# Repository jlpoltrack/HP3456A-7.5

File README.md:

# HP 3456A 7.5-Digit Firmware, Fixed

A corrected build of the community 7.5-digit firmware for the HP 3456A digital voltmeter.

The 7.5-digit mod, shared in the EEVblog thread "Adventures in retrocomputing"
(`3456AFirmware.zip`), shows a 7th digit at 10 and 100 PLC. Its published ROM also has seven
bugs. They crept in when the disassembly was restructured, and the best known is an **autorange
freeze**. This build fixes all seven, keeps the 7.5-digit feature, and tightens when the 7th
digit appears.

**Status:** tested on a real meter on 2026-10-19. All front-panel tests pass; see
[`docs/HARDWARE_VALIDATION.md`](docs/HARDWARE_VALIDATION.md). HPIB output of the 7th digit
has not been tested on hardware yet.

## What you get

- **7th digit** at 10 and 100 PLC, in the display's exponent position.
- **Autorange that works:** the meter ranges up and down without freezing.
- **Factory behaviour restored** for error 4 on bad digit counts, the dBm reference, NULL, the
  R and U presets, and storing the delay register D.

## Using 7-digit mode

Set 10 or 100 PLC, then enter `7` for digits displayed. The 7th digit is hidden, and the meter
behaves as a stock 6.5-digit unit, when:

- PLC is 1 or lower (the extra digit would only be noise);
- a number is being entered on the keypad or over HPIB.

### Reading the display

The 7th digit replaces the exponent, and the exponent sign is blank. Read the six mantissa digits
and append the 7th.

- **One decimal point lit:** no exponent is hidden, so read the value as shown.
- **Every decimal point lit except one:** the 7th digit is hiding an exponent. The digit with
  the **dark** decimal point is the true decimal position. The exponent is whatever the same
  range shows at 1 PLC, so check it once for each range you use.

Example: DCV, 100 mV range, shorted input, 10 PLC, 7 digits:

```
display   - 0. 0  0. 0. 0. 4.   7      dark DP after digit 2; at 1 PLC the range shows E-3
reads     -00.00047 E-3 V  = -0.47 µV  (10 nV resolution)
```

## Bugs fixed

None of these are in the factory ROM. Each was found by comparing against the factory `u7.bin`
and is tagged `FIX:` in [`src/u7fixed.asm`](src/u7fixed.asm).

| Where | Bug | Effect in the published ROM |
| --- | --- | --- |
| `sub012` (LA70F, LA724) | `jmp LC9D2` (main-loop restart) instead of `rts` | **Autorange freeze:** the new range never reaches the inguard |
| Power-on init (LD9A1) | 600 Ω preset written to the null register Z instead of R | Z = 600 and R = 0 after power-on |
| `subMathFcnDBM` | Tests Z instead of R for zero | The dBm guard checks the wrong register |
| `subPresetLnUregs` | U exponent written to U5 instead of U6 | Upper limit U is wrong (should be +1.999999E9) |
| RECALL key (LF4B8) | Clears Z0 instead of R0 | Wrong register cleared |
| Register D entry (LE0BC) | `bcc LE191` became an unconditional `jmp LE191` | Valid delay values are never stored |
| Digits-displayed entry (LE1DE) | `jsr subDisplayError4` dropped | Entering 2 or 8 is silently ignored instead of showing E4 |

The 7th-digit display and HPIB output now go through one routine, `sub7thDigitShown`, which
applies the PLC and number-entry rules above.

## Build

Requires Python 3.

```
python3 tools/as02.py src/u7fixed.asm build/u7fixed.bin build/u7fixed.lst
```

`build/u7fixed.bin` is a 32 KB image for U7, with the same layout as the original. For a larger
chip, tile it so the image works whatever the unused upper address lines are tied to:

```
python3 tools/replicate.py build/u7fixed.bin build/u7fixed_512K.bin 512K
```

Expected hashes for the tested build are listed in `docs/HARDWARE_VALIDATION.md`.

## Install

The validated meter uses an SST39SF040 flash chip, wired as a 27256-style ROM in the 28-pin U7
socket on the A4 controller board, and programmed with a TL866 (`minipro`). Wiring, continuity
checks and programming commands are in
[`docs/U7_FLASH_ADAPTER.md`](docs/U7_FLASH_ADAPTER.md). A PCB adapter that keeps the chip stock is in
[`hardware/u7-adapter/`](hardware/u7-adapter/) (designed, not yet built).

Before you install:

- **Back up the current chip** first (`minipro -p SST39SF040 -r backup.bin`).
- **Run the self-test** after installing. TEST cycles all segments on and off continuously
  until you press another key; a failure breaks the cycle and shows an error.

## ROM space

About 950 bytes are free for future changes:

| Range | Bytes | Notes |
| --- | --- | --- |
| $F33E–$F65A | 797 | Directly after the code |
| $FF56–$FFEF | 154 | Below the interrupt vectors |
| $8000–$9FFF | 8192 | Never used by the factory ROM; whether the board maps it to U7 is unverified |

### Ideas for the free space

Contributions welcome. Sizes are rough estimates.

| Idea | Size | Why |
| --- | --- | --- |
| Firmware version at power-on (e.g. `FIX 1` after `+HP3456+`) | ~30 B | Tells you which ROM a meter is running |
| ROM checksum in self-test | ~60 B | Catches a bad flash or failing chip, which the current self-test can't |
| Power-on defaults (e.g. 10 PLC, 7 digits) | ~20 B | The meter has no settings memory |
| ppm deviation math mode | ~150–250 B | % error has too few digits for 7.5-digit drift and calibration work |
| Stability indicator | ~100–150 B | Annunciator lights once the last N readings agree within X counts |
| Min/max hold | ~100 B | Track the extremes, viewable with RECALL L / U |
| Pt100 RTD temperature | ~300–400 B | 4-wire ohms to °C (Callendar–Van Dusen), using the ROM's BCD maths |

The first three fit together in the 154-byte block below the vectors, leaving the 797-byte
block for one larger feature.

To try out code in $8000–$9FFF, a [One ROM](https://onerom.org/) Fire 28 in place of the flash
chip makes testing and rollback fast. See the end of `docs/HARDWARE_VALIDATION.md`.

## Repository layout

| Path | Contents |
| --- | --- |
| `src/u7fixed.asm` | Fixed source; changes tagged `FIX:` (this build) and `MODDED` (the original 7.5-digit mod) |
| `src/u7modded.asm` | The published mod's source, recovered from its listing (the zip has no `.asm`); reassembles byte-identical to `u7modded.bin` |
| `tools/as02.py` | 6800 assembler for the AS02 subset used here, with branch relaxation |
| `tools/compare.py` | Lockstep semantic diff of two ROMs: `compare.py orig.bin new.bin new.lst`. Run it against the factory `u7.bin` |
| `tools/dis.py` | Linear 6800 disassembler: `dis.py rom.bin start end` |
| `tools/replicate.py` | Tiles an image to fill a larger chip |
| `tools/lst2asm.py` | Recovers source from an AS02 listing |
| `tools/patch.py` | Earlier in-place binary patcher, superseded by the source build |
| `hardware/u7-adapter/` | KiCad project for the U7 flash adapter PCB: SST39SF040 socket on a DIP-28 plug, bank jumpers |
| `docs/` | Flash adapter wiring, the hardware test plan with results, and the [HP-IB command reference](docs/GPIB_COMMANDS.md) |

## Credits, license and disclaimer

The disassembly, commentary and 7.5-digit mod come from the work shared in the EEVblog
"Adventures in retrocomputing" thread. This project only fixes and extends it. The original
firmware is HP's.

This project's own work (the tools, the docs and the `FIX:` changes) is MIT-licensed; see
[`LICENSE`](LICENSE). The licence doesn't cover HP's firmware or the upstream mod. No ROM
images are included: get `3456AFirmware.zip` from the thread, then build from source.

Use at your own risk. Back up your original ROM, and work only on the outguard controller
board with the meter unplugged.

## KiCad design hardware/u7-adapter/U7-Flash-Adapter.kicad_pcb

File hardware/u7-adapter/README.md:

# U7 Flash Adapter

A small PCB that runs an SST39SF040 flash chip in the 28-pin U7 socket of the HP 3456A A4 controller
board. It replaces the hand-wired chip in [`docs/U7_FLASH_ADAPTER.md`](../../docs/U7_FLASH_ADAPTER.md):
the flash chip stays stock, so it moves between the adapter and the TL866 without bending any legs.

**Status (2026-10-24):** V1.0, designed and checked (DRC, ERC and lint all clean). Not yet ordered
or tested in a meter. See [Open items](#open-items) before ordering.

| Front | Back |
| --- | --- |
|  |  |

## How it works

- **Plug (J2):** a DIP-28 pin pattern under the board plugs into U7. It uses the 27256 pinout,
  and pin 1 (VPP) is not connected.
- **Socket (U1):** the 32-pin socket sits 5.1 mm to the right of the plug and two rows higher, so
  plug pin *n* and flash pin *n*+2 share a row. All 26 signals and GND are one straight trace each.
- **Read-only:** WE# is tied to +5V, so the chip is never written in the meter.
- **Power:** there are two ways to feed +5V, and the board ships with neither connected.
  - **JP1** (silk `P28`) joins U7 pin 28 to +5V. It is open as built. Bridge it only after U7
    pin 28 measures +5 V with the meter on and the chip out. Nobody has checked yet what the A4
    board puts on that pin.
  - **TP1** (silk `C1+`) is a wire pad. Run a wire from it to the + end of the meter's C1, the
    same way the hand-wired chip is powered.

  C1 on the adapter (100 nF) decouples U1 pin 32.
- **Bank select (J1):** 10k resistors (R1–R4) pull A15–A18 low, so with no jumpers the chip reads
  bank 0 (the first 32K). A jumper from an A pin to the 5V pin above it sets that bit to 1.
  Bank *n* is the 32K block at offset *n* × $8000. The columns are labelled A18 A16 A15 A17, in
  routing order. `u7fixed_512K.bin` repeats the image in all 16 banks, so jumpers only matter if
  you store different images.

## Parts

| Ref | Part | Notes |
| --- | --- | --- |
| U1 | 32-pin 600 mil turned-pin DIP socket | holds the SST39SF040 |
| J2 | 28-pin 600 mil DIP plug: two 1x14 machined male pin strips, or a machined-pin DIP header | soldered from the bottom, long pins down into U7 |
| J1 | 2x4 pin header, 2.54 mm, plus jumpers | bank select |
| R1–R4 | 10k, 0805 | A15–A18 pull-downs |
| C1 | 100 nF, 0805, 25 V or more | decoupling |
| JP1 | solder jumper (on the PCB) | U7 pin 28 to +5V |
| TP1 | wire pad (on the PCB) | +5V from the meter's C1 |

A plain DIP socket can't be J2: its pins are too short to reach through the board into U7, and a
long-tail (wire-wrap) socket would need its body on top, where U1 sits.

## Assembly

1. Solder the 0805 parts (R1–R4, C1) first.
2. Fit J1.
3. Fit U1 on the top.
4. Fit J2 from the bottom, with the long pins pointing down. Solder J2 on the top, inside U1's
   open frame, before the chip goes in. The B silk shows J2's outline and pin-1 notch.
5. Power: either bridge JP1 (only once pin 28 is confirmed as +5 V), or wire TP1 to the meter's C1.
6. Before fitting it in the meter, with no chip in, check for no short from +5V to GND. Then check
   each J2 pin to its U1 pin, n to n+2.

U1's notch and J2's pin 1 both face the same end, toward the board edge as the chip sits now.

## Fabrication

2-layer, 1.6 mm, 29.4 x 54.2 mm, JLC default rules. Gerbers and drill files are in
`production/HP_3456A_U7_Flash_Adapter_1.0.zip`. It's a bare-PCB order: all parts are hand-soldered,
and the BOM and positions files are not needed. Five boards cost about $4 plus shipping.

## Files

| Path | Contents |
| --- | --- |
| `U7-Flash-Adapter.kicad_sch` / `.kicad_pcb` | KiCad 10 project |
| `U7-Flash-Adapter.pdf` | schematic |
| `production/` | gerbers and drill files (zip), BOM, positions |
| `renders/Routing-*.png`, `Render-Copper.png` | copper views |
| `style_lint.ignore` | accepted lint items (parts aligned to the 2.54 mm pin rows, off the 0.1 mm grid) |

The schematic and board were generated by scripts in the author's (private) kicad-tools repo
(`projects/u7-adapter/`). Edit the KiCad files directly; they are the source of truth here.
`pth_inside_courtyard` is set to ignore in the project, because the plug and the socket overlap by
design.

## Open items

- [ ] Measure U7 pin 28 against pin 14 with the chip out and the meter on, to decide JP1 or TP1.
- [ ] Measure the clearance around U7. The adapter overhangs U7: the board reaches about 5 mm past
      the plug on the right (the socket and C1 strip) and 18 mm past pin 1 (the bank header). It
      also sits about 12 mm higher than the bare chip.
- [ ] Order the PCB, build one, and run the checks in `docs/HARDWARE_VALIDATION.md`.

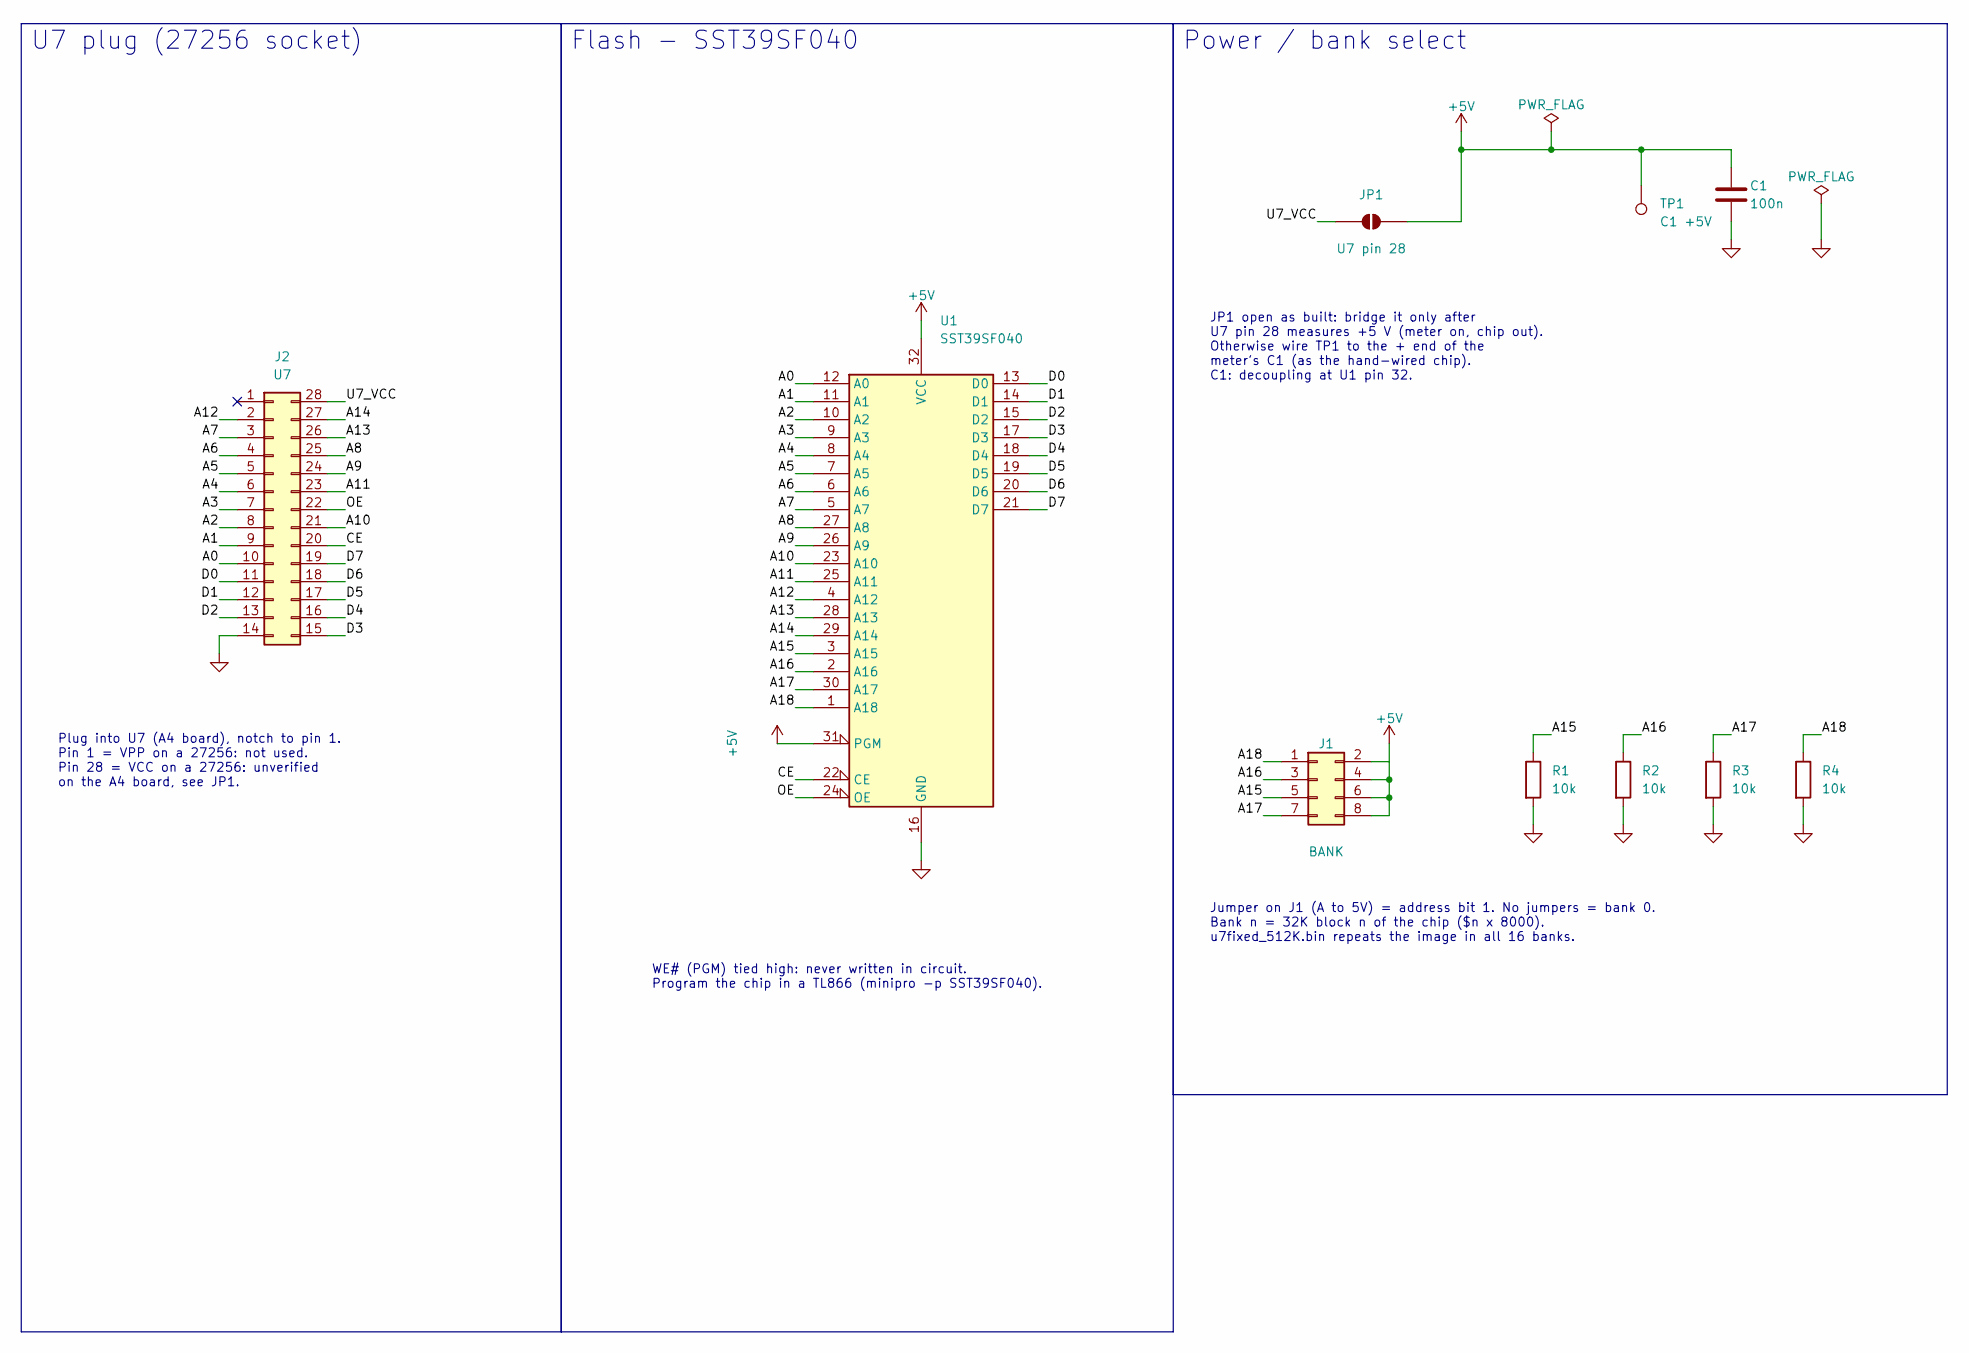
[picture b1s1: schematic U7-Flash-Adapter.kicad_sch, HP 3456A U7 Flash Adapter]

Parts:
C1: 100n; C_0805_2012Metric_Pad1.18x1.45mm_HandSolder
J1: BANK; PinHeader_2x04_P2.54mm_Vertical
J2: U7; DIP-28_W15.24mm_Plug
JP1: U7 pin 28; SolderJumper-2_P1.3mm_Open_TrianglePad1.0x1.5mm
R1, R2, R3, R4: 10k; R_0805_2012Metric_Pad1.20x1.40mm_HandSolder
TP1: C1 +5V; TestPoint_THTPad_D2.0mm_Drill1.0mm
U1: SST39SF040; DIP-32_W15.24mm_Socket

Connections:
+5V: C1.1, J1.2, J1.4, J1.6, J1.8, JP1.2 (B), TP1.1 (1_1), U1.31 (PGM), U1.32 (VCC)
/A0: J2.10, U1.12 (A0)
/A1: J2.9, U1.11 (A1)
/A2: J2.8, U1.10 (A2)
/A3: J2.7, U1.9 (A3)
/A4: J2.6, U1.8 (A4)
/A5: J2.5, U1.7 (A5)
/A6: J2.4, U1.6 (A6)
/A7: J2.3, U1.5 (A7)
/A8: J2.25, U1.27 (A8)
/A9: J2.24, U1.26 (A9)
/A10: J2.21, U1.23 (A10)
/A11: J2.23, U1.25 (A11)
/A12: J2.2, U1.4 (A12)
/A13: J2.26, U1.28 (A13)
/A14: J2.27, U1.29 (A14)
/A15: J1.5, R1.1, U1.3 (A15)
/A16: J1.3, R2.1, U1.2 (A16)
/A17: J1.7, R3.1, U1.30 (A17)
/A18: J1.1, R4.1, U1.1 (A18)
/CE: J2.20, U1.22 (CE)
/D0: J2.11, U1.13 (D0)
/D1: J2.12, U1.14 (D1)
/D2: J2.13, U1.15 (D2)
/D3: J2.15, U1.17 (D3)
/D4: J2.16, U1.18 (D4)
/D5: J2.17, U1.19 (D5)
/D6: J2.18, U1.20 (D6)
/D7: J2.19, U1.21 (D7)
/OE: J2.22, U1.24 (OE)
/U7_VCC: J2.28, JP1.1 (A)
GND: C1.2, J2.14, R1.2, R2.2, R3.2, R4.2, U1.16 (GND)

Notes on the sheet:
U7 plug (27256 socket)
Flash - SST39SF040
Power / bank select
Plug into U7 (A4 board), notch to pin 1. Pin 1 = VPP on a 27256: not used. Pin 28 = VCC on a 27256: unverified on the A4 board, see JP1.
WE# (PGM) tied high: never written in circuit. Program the chip in a TL866 (minipro -p SST39SF040).
JP1 open as built: bridge it only after U7 pin 28 measures +5 V (meter on, chip out). Otherwise wire TP1 to the + end of the meter's C1 (as the hand-wired chip). C1: decoupling at U1 pin 32.
Jumper on J1 (A to 5V) = address bit 1. No jumpers = bank 0. Bank n = 32K block n of the chip ($n x 8000). u7fixed_512K.bin repeats the image in all 16 banks.

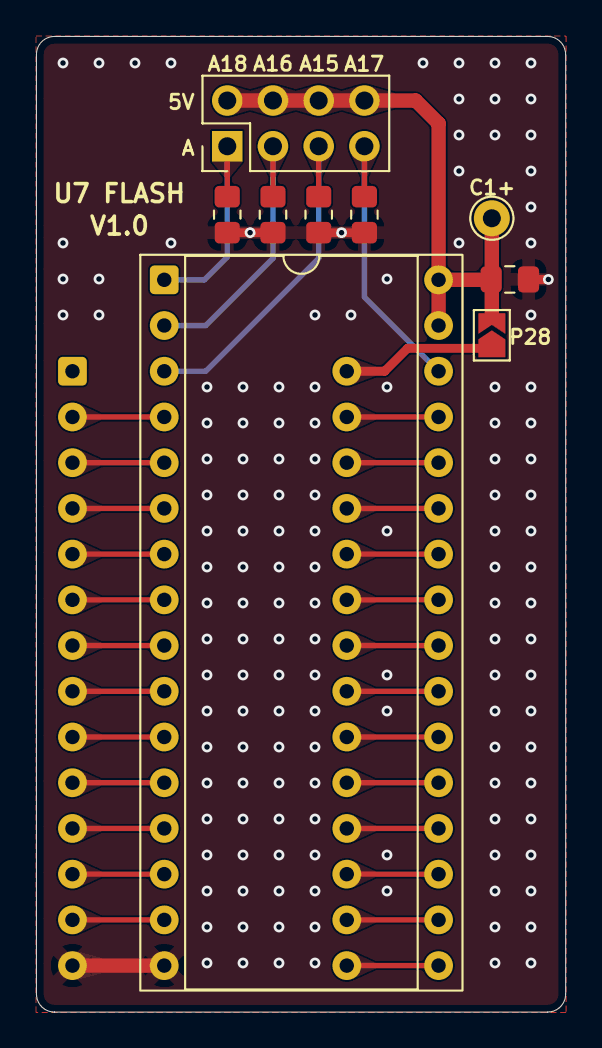
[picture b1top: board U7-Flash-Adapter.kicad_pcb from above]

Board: 2 copper layers, 29.4 x 54.2 mm, 14 parts (0 on the bottom side), 32 nets.

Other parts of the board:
LOGO1, LOGO2, LOGO3, LOGO4: title

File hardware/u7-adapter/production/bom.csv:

Designator,Footprint,Quantity,Value,LCSC Part #
C1,0805,1,100n,
J1,PinHeader_2x04_P2.54mm_Vertical,1,BANK,
J2,DIP-28_W15.24mm_Plug,1,U7,
"R1, R2, R3, R4",0805,4,10k,
U1,DIP-32_W15.24mm_Socket,1,SST39SF040,

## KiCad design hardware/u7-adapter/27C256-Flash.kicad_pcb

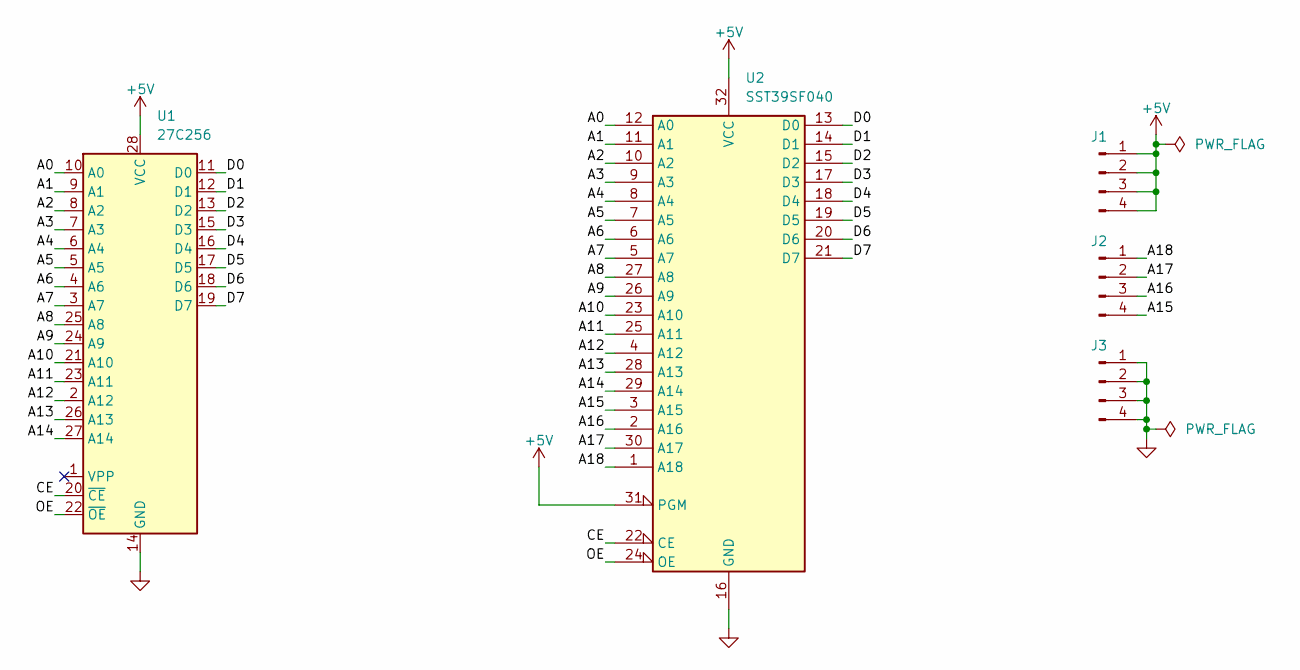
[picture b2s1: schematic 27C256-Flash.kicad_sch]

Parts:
J1, J2, J3: Conn_01x04_Pin; PinHeader_1x04_P2.54mm_Vertical
U1: 27C256; DIP-28_W15.24mm
U2: SST39SF040; DIP-32_W15.24mm_Socket

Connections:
+5V: J1.1, J1.2, J1.3, J1.4, U1.28 (VCC), U2.31 (PGM), U2.32 (VCC)
/A0: U1.10 (A0), U2.12 (A0)
/A1: U1.9 (A1), U2.11 (A1)
/A2: U1.8 (A2), U2.10 (A2)
/A3: U1.7 (A3), U2.9 (A3)
/A4: U1.6 (A4), U2.8 (A4)
/A5: U1.5 (A5), U2.7 (A5)
/A6: U1.4 (A6), U2.6 (A6)
/A7: U1.3 (A7), U2.5 (A7)
/A8: U1.25 (A8), U2.27 (A8)
/A9: U1.24 (A9), U2.26 (A9)
/A10: U1.21 (A10), U2.23 (A10)
/A11: U1.23 (A11), U2.25 (A11)
/A12: U1.2 (A12), U2.4 (A12)
/A13: U1.26 (A13), U2.28 (A13)
/A14: U1.27 (A14), U2.29 (A14)
/A15: J2.4, U2.3 (A15)
/A16: J2.3, U2.2 (A16)
/A17: J2.2, U2.30 (A17)
/A18: J2.1, U2.1 (A18)
/CE: U1.20 (~CE), U2.22 (CE)
/D0: U1.11 (D0), U2.13 (D0)
/D1: U1.12 (D1), U2.14 (D1)
/D2: U1.13 (D2), U2.15 (D2)
/D3: U1.15 (D3), U2.17 (D3)
/D4: U1.16 (D4), U2.18 (D4)
/D5: U1.17 (D5), U2.19 (D5)
/D6: U1.18 (D6), U2.20 (D6)
/D7: U1.19 (D7), U2.21 (D7)
/OE: U1.22 (~OE), U2.24 (OE)
GND: J3.1, J3.2, J3.3, J3.4, U1.14 (GND), U2.16 (GND)

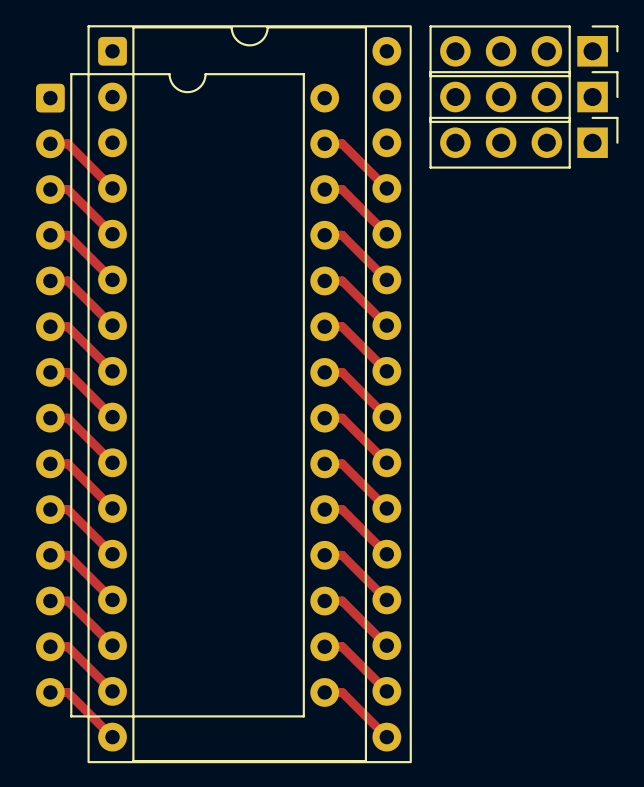
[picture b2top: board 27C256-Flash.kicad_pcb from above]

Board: 2 copper layers, 5 parts (0 on the bottom side), 31 nets.
